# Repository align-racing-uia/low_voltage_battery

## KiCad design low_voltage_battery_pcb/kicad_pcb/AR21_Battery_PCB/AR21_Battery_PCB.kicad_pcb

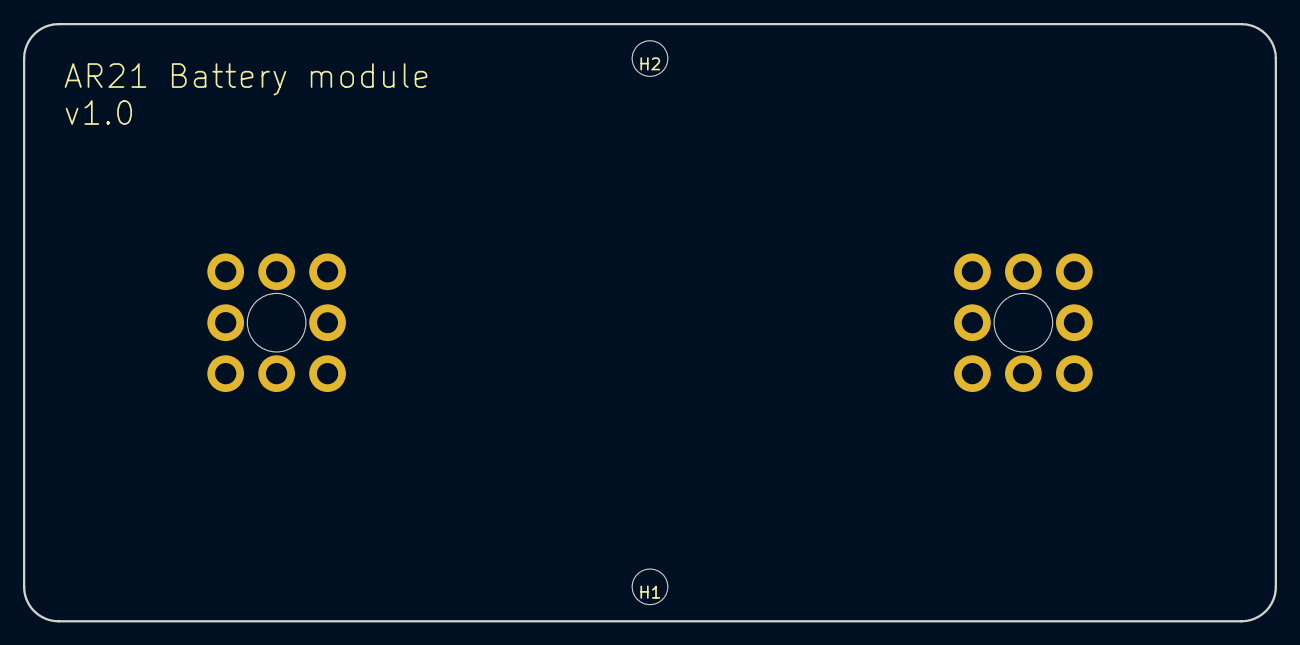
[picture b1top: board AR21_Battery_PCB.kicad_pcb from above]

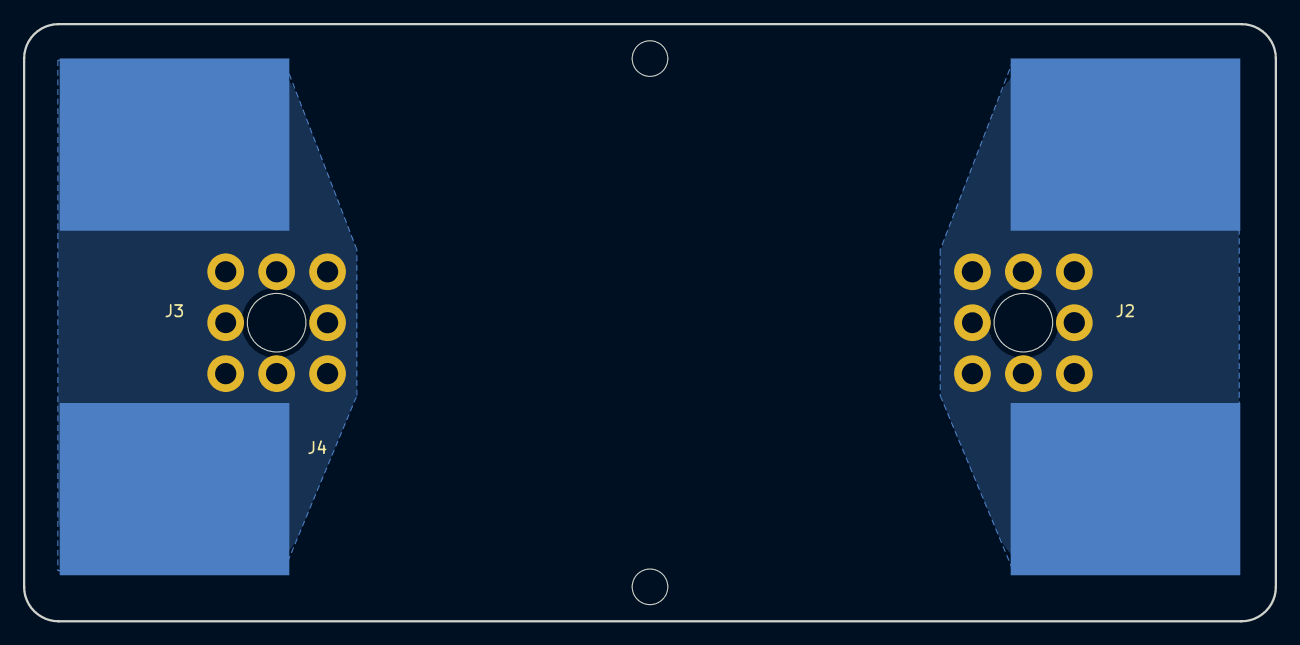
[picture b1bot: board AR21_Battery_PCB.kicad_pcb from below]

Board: 2 copper layers, 109.0 x 52.0 mm, 6 parts (2 on the bottom side), 2 nets, no tracks yet.

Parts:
H1, H2: MountingHole; M3 hole
J1, J4: Conn_01x01_Female; Wurth_74655095R_Screw_Post
J2, J3: Conn_01x01_Male; Flat

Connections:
Negative: J3.1, J4.1
Positive: J1.1, J2.1

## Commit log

2021-08-01 Directory refactor, and adjustment of README.md
2021-08-01 Minor directory move.
